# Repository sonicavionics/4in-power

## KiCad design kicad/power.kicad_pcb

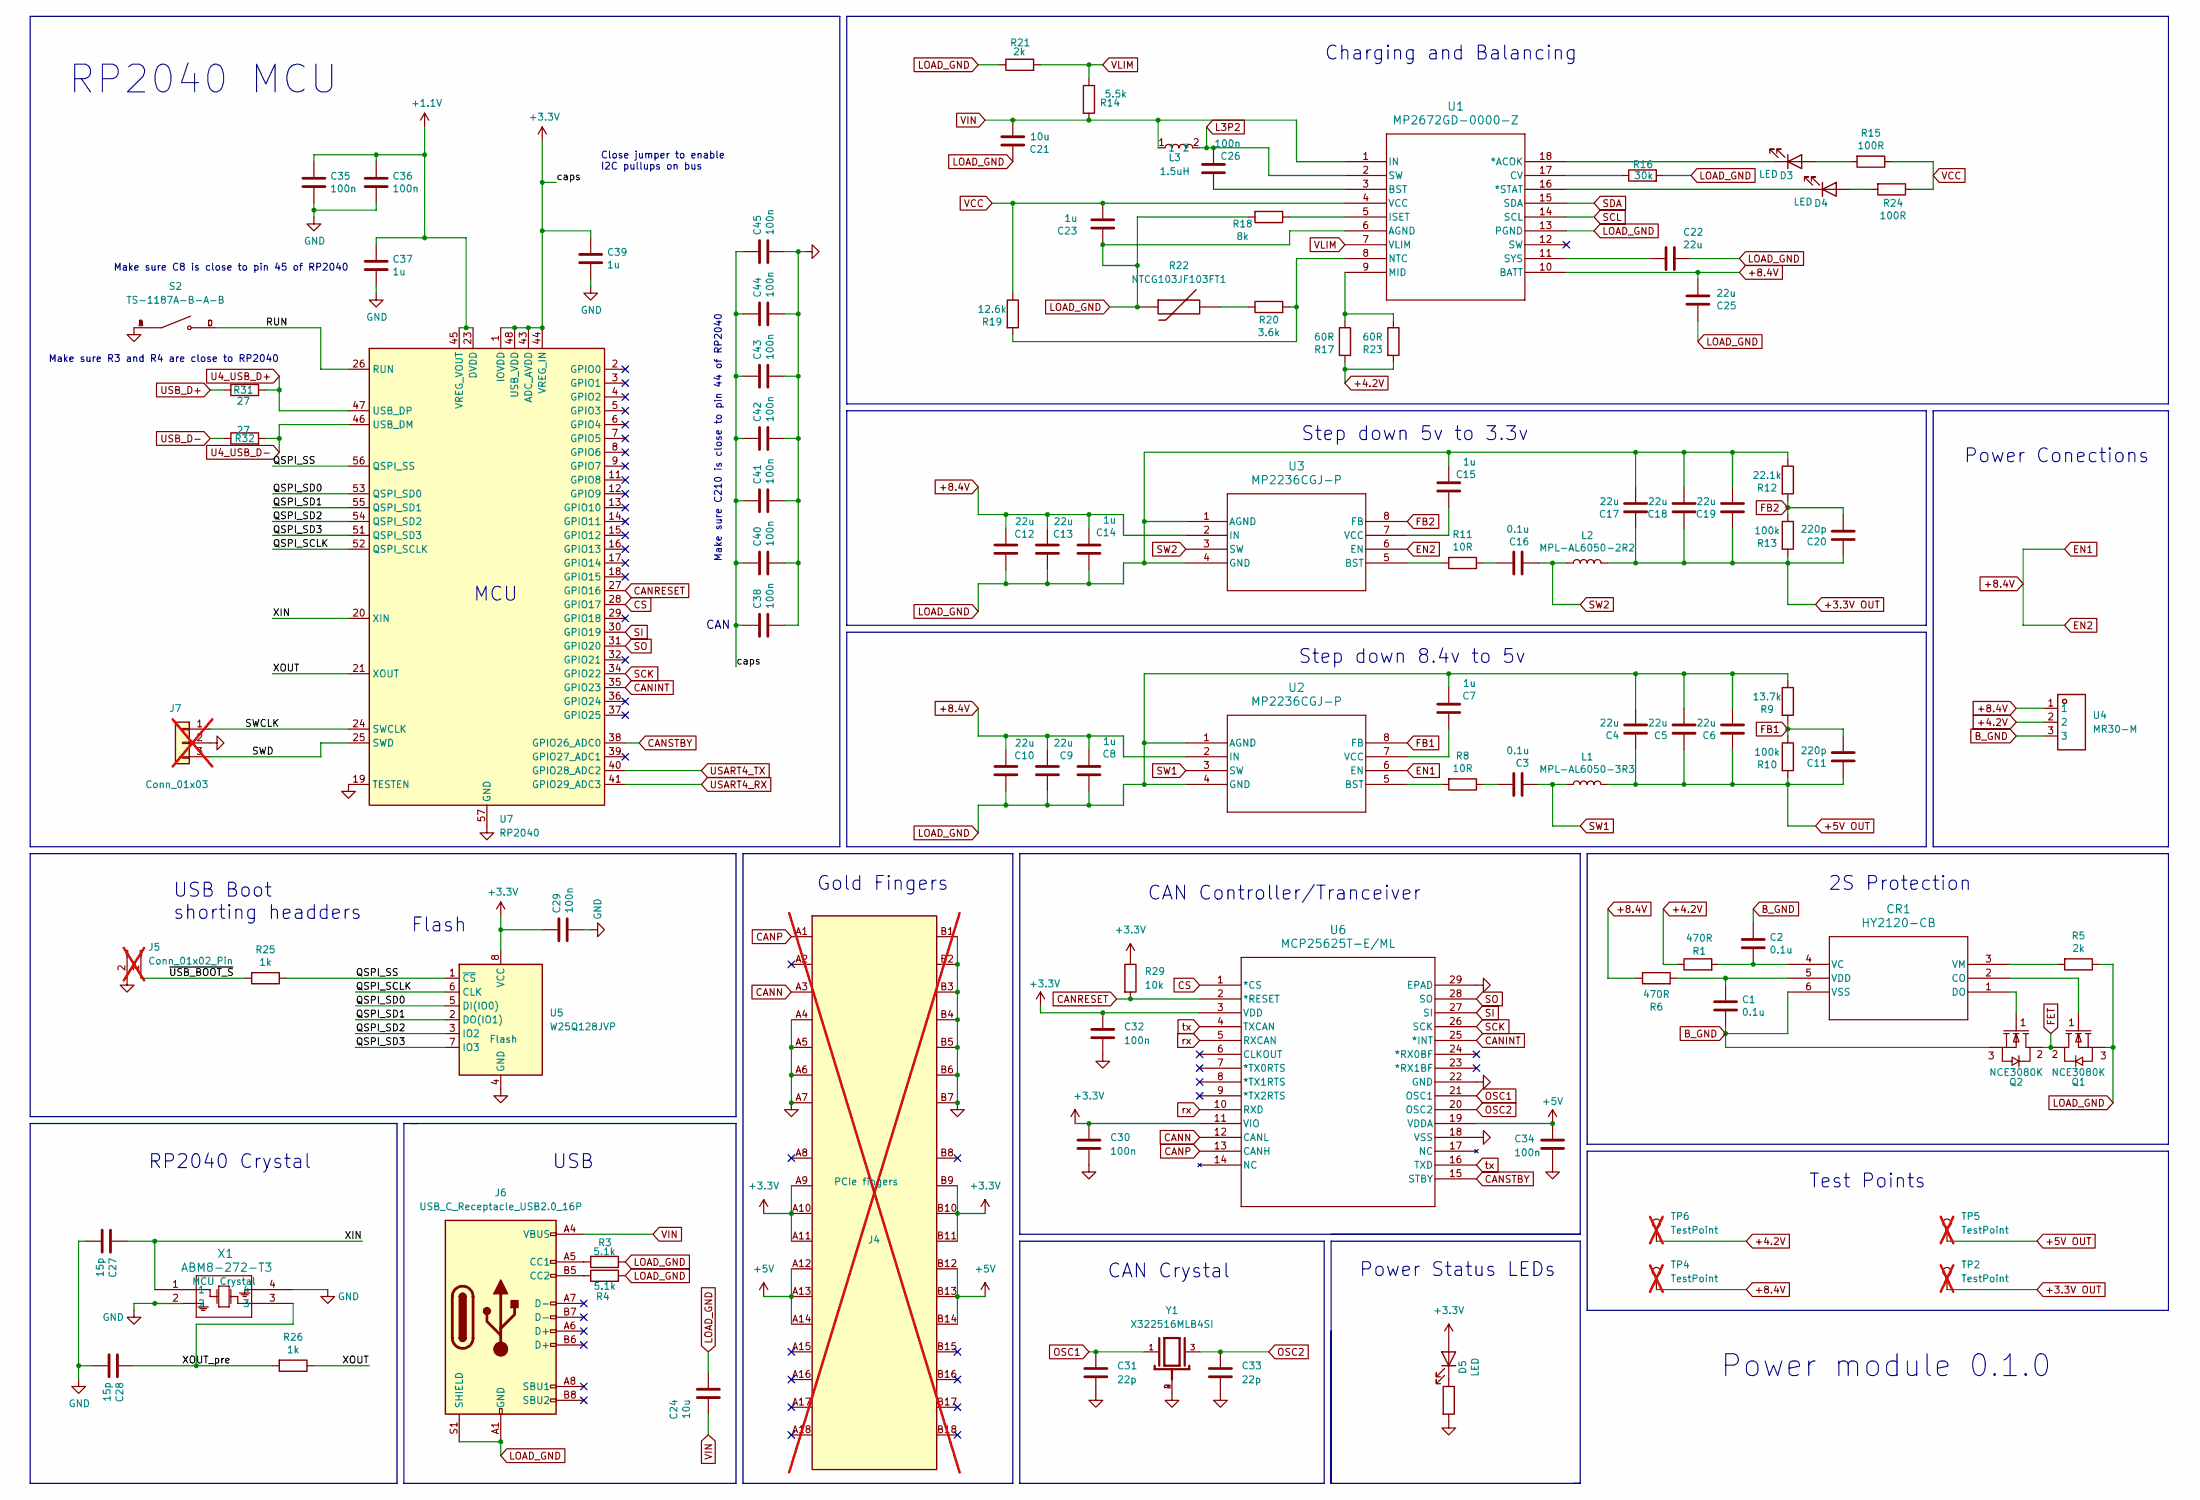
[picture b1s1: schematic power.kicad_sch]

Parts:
C1, C2, C16: 0.1u; C_0603_1608Metric
C3: 0.1u; C_0402_1005Metric
C4, C5, C6, C9, C10: 22u; C_0402_1005Metric
C7, C8, C37, C39: 1u; C_0402_1005Metric; LCSC Part # C52923
C11: 220p; C_0402_1005Metric
C12, C13, C17, C18, C19, C22: 22u; C_0805_2012Metric
C14: 1u; C_0805_2012Metric; LCSC Part # C52923
C15, C23: 1u; C_0603_1608Metric; LCSC Part # C52923
C20: 220p; C_0603_1608Metric
C21, C24: 10u; C_0805_2012Metric
C25: 22u; C_1206_3216Metric
C26: 100n; C_0603_1608Metric
C27, C28: 15p; C_0402_1005Metric; LCSC Part # C1548
C29, C30, C32, C34, C35, C36, C38, C40, C41, C42, C43, C44, C45: 100n; C_0402_1005Metric; LCSC Part # C307331
C31, C33: 22p; C_0402_1005Metric; LCSC Part # C1555
CR1: HY2120-CB; SOT-23-6; LCSC Part # C116509
D3, D5: LED; LED_0603_1608Metric; LCSC Part # C2286
D4: LED; LED_0603_1608Metric; LCSC Part # C2288
J4: Bus_PCI_Express_x1; BUS_PCIexpress_x1; LCSC Part # n/a; not fitted
J5: Conn_01x02_Pin; PinHeader_1x02_P2.54mm_Vertical; not fitted
J6: USB_C_Receptacle_USB2.0_16P; USB_C_Receptacle_Palconn_UTC16-G; LCSC Part # C2765186
J7: Conn_01x03; PinHeader_1x03_P2.54mm_Vertical; LCSC Part # n/a; not fitted
L1: MPL-AL6050-3R3; 2-SMD
L2: MPL-AL6050-2R2; 2-SMD
L3: 1.5uH; IND-SMD_L7.0-W6.6; TOLERANCE ±20%; MANUFACTURER PART MWSA0605S-1R5MT; LCSC PART NAME 1.5uH ±20% 13A
Q1, Q2: NCE3080K; TO-252-2_L6.6-W6.1-P4.57-LS9.9-TL-CW; LCSC Part # C108901
R1, R6: 470R; R_1206_3216Metric
R3, R4: 5.1k; R_0402_1005Metric; LCSC Part # C25905
R5, R21: 2k; R_0603_1608Metric
R8: 10R; R_0402_1005Metric
R9: 13.7k; R_0402_1005Metric
R10: 100k; R_0402_1005Metric
R11: 10R; R_1206_3216Metric
R12: 22.1k; R_0603_1608Metric
R13: 100k; R_0603_1608Metric
R14: 5.5k; R_0603_1608Metric
R15, R24: 100R; R_0805_2012Metric
R16: 30k; R_0603_1608Metric
R17, R23: 60R; R_1206_3216Metric
R18: 8k; R_0603_1608Metric
R19: 12.6k; R_0603_1608Metric
R20: 3.6k; R_0603_1608Metric
R22: NTCG103JF103FT1; D_0402_1005Metric; MANUFACTURER PART NTCG103JF103FT1; LCSC PART NAME 10kΩ 电阻精度:±1% 3380K
R25, R26: 1k; R_0402_1005Metric; LCSC Part # C11702
R29: 10k; R_0402_1005Metric; LCSC Part # C25744
R30: 1 k; R_0603_1608Metric; Manufacturer_Part_Number 0603WAF1001T5E; Mouser Part Number 950-0603WAF1001T5E
R31, R32: 27; R_0402_1005Metric; LCSC Part # C25100
S2: TS-1187A-B-A-B; SW_TS-1187A-B-A-B; PARTREV A0; LCSC Part # C318884
TP2, TP4, TP5, TP6: TestPoint; PinHeader_1x01_P2.54mm_Vertical; not fitted
U1: MP2672GD-0000-Z; QFN-18_2MMx3MM_MP2672_MNP_MPS
U2, U3: MP2236CGJ-P; TSOT23-8_MP2236C_MNP
U4: MR30-M; CONN-TH_MR30-M; MANUFACTURER PART MR30-M; LCSC PART NAME AMASS(艾迈斯)锂电池三芯电源连接器公头MR30-M 2件套
U5: W25Q128JVP; WSON-8-1EP_6x5mm_P1.27mm_EP3.4x4.3mm; LCSC C190862
U6: MCP25625T-E/ML; QFN28_6X6MC_MCH; LCSC Part # C191253
U7: RP2040; QFN-56-1EP_7x7mm_P0.4mm_EP3.2x3.2mm; LCSC C2040
X1: ABM8-272-T3; ABM8-272-T3_ABR; LCSC Part # C20625731
Y1: X322516MLB4SI; OSC_X322516MLB4SI; PARTREV N/A; LCSC Part # C12668

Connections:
+1.1V: C35.1, C36.1, C37.1, U7.23 (DVDD), U7.45 (VREG_VOUT), U7.50 (DVDD)
+3.3V: C29.1, C30.1, C32.1, C38.1, C39.1, C40.1, C41.1, C42.1, C43.1, C44.1, C45.1, D5.2 (A), J4.A9 (+3.3V), J4.A10 (+3.3V), J4.A11 (~PERST), J4.B9 (JTAG1), J4.B10 (3.3Vaux), J4.B11 (~WAKE), R29.1, U5.8 (VCC), U6.3 (VDD), U6.11 (VIO), U7.1 (IOVDD), U7.10 (IOVDD), U7.22 (IOVDD), U7.33 (IOVDD), U7.42 (IOVDD), U7.43 (ADC_AVDD), U7.44 (VREG_IN), U7.48 (USB_VDD), U7.49 (IOVDD)
+3.3V OUT: C17.1, C18.1, C19.1, C20.1, L2.2, R13.2, TP2.1
+4.2V: R1.1, R17.2, R23.2, TP6.1, U4.2
+5V: C34.1, J4.A12 (GND), J4.A13 (REFCLK+), J4.A14 (REFCLK-), J4.B12 (RSVD), J4.B13 (GND), J4.B14 (PETp0), U6.19 (VDDA)
+5V OUT: C4.1, C5.1, C6.1, C11.1, L1.2, R10.2, TP5.1
+8.4V: C8.1, C9.2, C10.2, C12.2, C13.2, C14.1, C25.1, R6.1, TP4.1, U1.10 (BATT), U2.2 (IN), U2.6 (EN), U3.2 (IN), U3.6 (EN), U4.1
/QSPI_SCLK: U5.6 (CLK), U7.52 (QSPI_SCLK)
/QSPI_SD0: U5.5 (DI(IO0)), U7.53 (QSPI_SD0)
/QSPI_SD1: U5.2 (DO(IO1)), U7.55 (QSPI_SD1)
/QSPI_SD2: U5.3 (IO2), U7.54 (QSPI_SD2)
/QSPI_SD3: U5.7 (IO3), U7.51 (QSPI_SD3)
/QSPI_SS: R25.1, U5.1 (~CS), U7.56 (QSPI_SS)
/RUN: S2.C, S2.D, U7.26 (RUN)
/SWCLK: J7.1, U7.24 (SWCLK)
/SWD: J7.3, U7.25 (SWD)
/XIN: C27.1, U7.20 (XIN), X1.1
/XOUT: R26.1, U7.21 (XOUT)
/XOUT_pre: C28.1, R26.2, X1.3
/~USB_BOOT_S: J5.1, R25.2
B_GND: C1.2, C2.1, CR1.6 (VSS), Q2.3 (S), U4.3
CANINT: U6.25 (*INT), U7.35 (GPIO23)
CANN: J4.A3 (+12V), U6.12 (CANL)
CANP: J4.A1 (~PRSNT1), U6.13 (CANH)
CANRESET: R29.2, U6.2 (*RESET), U7.27 (GPIO16)
CANSTBY: U6.15 (STBY), U7.38 (GPIO26_ADC0)
CS: U6.1 (*CS), U7.28 (GPIO17)
FB1: C11.2, R9.2, R10.1, U2.8 (FB)
FB2: C20.2, R12.2, R13.1, U3.8 (FB)
FET: Q1.2 (D), Q2.2 (D)
GND: C27.2, C28.2, C29.2, C30.2, C31.2, C32.2, C33.2, C34.2, C35.2, C36.2, C37.2, C38.2, C39.2, C40.2, C41.2, C42.2, C43.2, C44.2, C45.2, J4.A4 (GND), J4.A5 (JTAG2), J4.A6 (JTAG3), J4.A7 (JTAG4), J4.B1 (+12V), J4.B2 (+12V), J4.B3 (+12V), J4.B4 (GND), J4.B5 (SMCLK), J4.B6 (SMDAT), J4.B7 (GND), J5.2, J7.2, R30.2, S2.A, S2.B, U5.4 (GND), U6.18 (VSS), U6.22 (GND), U6.29 (EPAD), U7.19 (TESTEN), U7.57 (GND), X1.2, X1.4, Y1.2, Y1.4
L3P2: C26.1, L3.2, U1.2 (SW)
LOAD_GND: C4.2, C5.2, C6.2, C7.1, C8.2, C9.1, C10.1, C12.1, C13.1, C14.2, C15.1, C17.2, C18.2, C19.2, C21.2, C22.1, C23.2, C24.2, C25.2, J6.A1 (GND), J6.A12 (GND), J6.B1 (GND), J6.B12 (GND), J6.S1 (SHIELD), Q1.3 (S), R3.1, R4.2, R5.1, R9.1, R12.1, R16.2, R18.2, R21.1, R22.1, U1.6 (AGND), U1.13 (PGND), U2.1 (AGND), U2.4 (GND), U3.1 (AGND), U3.4 (GND)
unnamed: C3.1, R8.1
unnamed: C16.1, R11.1
unnamed: CR1.2 (CO), Q1.1 (G)
unnamed: CR1.1 (DO), Q2.1 (G)
unnamed: C2.2, CR1.4 (VC), R1.2
unnamed: C1.1, CR1.5 (VDD), R6.2
unnamed: CR1.3 (VM), R5.2
unnamed: D3.2 (A), R15.2
unnamed: D3.1 (K), U1.18 (*ACOK)
unnamed: D4.2 (A), R24.2
unnamed: D4.1 (K), U1.16 (*STAT)
unnamed: D5.1 (K), R30.1
unnamed: J6.A5 (CC1), R3.2
unnamed: J6.B5 (CC2), R4.1
unnamed: R20.1, R22.2
unnamed: C26.2, U1.3 (BST)
unnamed: R16.1, U1.17 (CV)
unnamed: R18.1, U1.5 (ISET)
unnamed: R17.1, R23.1, U1.9 (MID)
unnamed: R19.2, R20.2, U1.8 (NTC)
unnamed: C22.2, U1.11 (SYS)
unnamed: R8.2, U2.5 (BST)
unnamed: C7.2, U2.7 (VCC)
unnamed: R11.2, U3.5 (BST)
unnamed: C15.2, U3.7 (VCC)
OSC1: C31.1, U6.21 (OSC1), Y1.1
OSC2: C33.1, U6.20 (OSC2), Y1.3
SCK: U6.26 (SCK), U7.34 (GPIO22)
SCL: U1.14 (SCL)
SDA: U1.15 (SDA)
SI: U6.27 (SI), U7.30 (GPIO19)
SO: U6.28 (SO), U7.31 (GPIO20)
SW1: C3.2, L1.1, U2.3 (SW)
SW2: C16.2, L2.1, U3.3 (SW)
U4_USB_D+: R31.2, U7.47 (USB_DP)
U4_USB_D-: R32.2, U7.46 (USB_DM)
USART4_RX: U7.41 (GPIO29_ADC3)
USART4_TX: U7.40 (GPIO28_ADC2)
USB_D+: R31.1
USB_D-: R32.1
VCC: C23.1, R15.1, R19.1, R24.1, U1.4 (VCC)
VIN: C21.1, C24.1, J6.A4 (VBUS), J6.A9 (VBUS), J6.B4 (VBUS), J6.B9 (VBUS), L3.1, R14.2, U1.1 (IN)
VLIM: R14.1, R21.2, U1.7 (VLIM)
rx: U6.5 (RXCAN), U6.10 (RXD)
tx: U6.4 (TXCAN), U6.16 (TXD)

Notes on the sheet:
Flash
2S Protection
RP2040 Crystal
Make sure R3 and R4 are close to RP2040
CAN Crystal
Close jumper to enable I2C pullups on bus
Make sure C210 is close to pin 44 of RP2040
CAN Controller/Tranceiver
CAN
MCU
Power Status LEDs
Gold Fingers
Charging and Balancing
USB Boot shorting headders
Step down 5v to 3.3v
Power module 0.1.0
Power Conections
Test Points
RP2040 MCU
USB
Make sure C8 is close to pin 45 of RP2040
Step down 8.4v to 5v

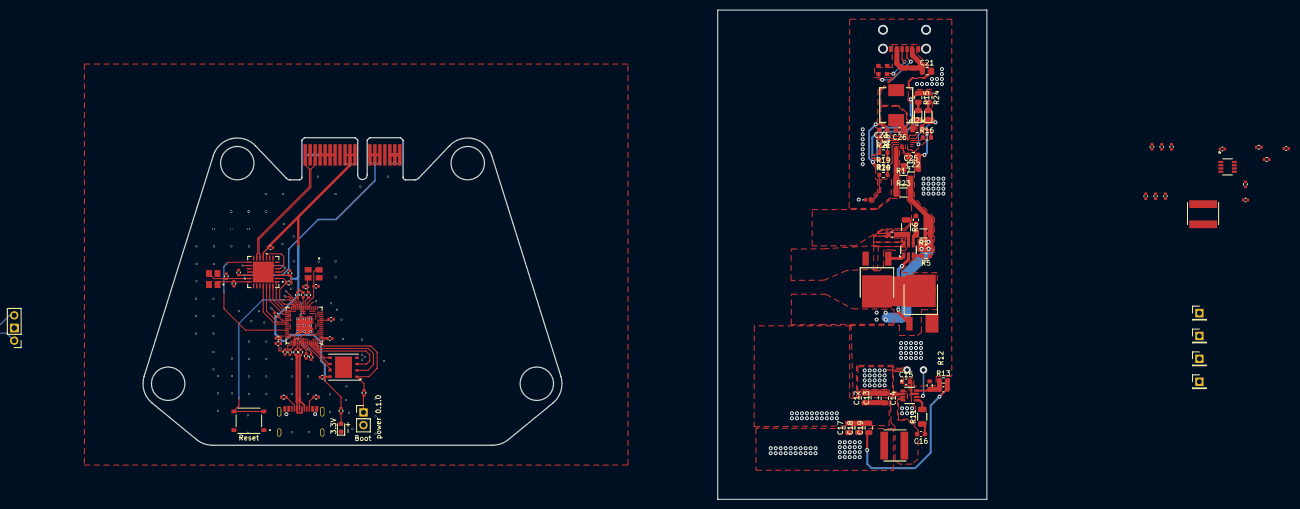
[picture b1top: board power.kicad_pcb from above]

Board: 2 copper layers, 169.4 x 98.2 mm, 99 parts (1 on the bottom side), 72 nets.

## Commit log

2025-06-12 Update files for KiCad 9.0 and general Schematic updates
2025-06-12 Update images
2025-06-12 Add MCU and CAN chips
2025-06-22 Update footprints
2025-06-22 Update component placement
2025-06-22 Update FETs and Protection IC
2025-06-22 Prototype BMS and Protection
2025-06-22 Fixing Zones
2025-06-22 Move MCU to the side
